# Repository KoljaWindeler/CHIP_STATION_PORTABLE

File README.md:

# CHIP_STATION_PORTABLE
This project is about a better and gaming compatible housing for C.H.I.P.

PocketChip is a great toy to play with, but the keys tend to be hard to push and make some hard click noises. 
The PSP seems like the perfect housing for a CHIP.

Just to mention some features:
 - it has a parallel display that was almost compatible with chip (only requires small amount of hardware)
 - many buttons (4 for the directions + 4 [x,y,a,b] + 2 shoulder buttons + menu buttons (vol+, vol-, ...) ..)
 - status LEDs for power / charging controllable on the LOW end (+5V is directly connected to the LED) 
 - 3.7V lipo battery which should work directly with chips battery circuit
 - 5V input for charging, perfect for chip
 
The purpose of this project is to create a mainboard that acts as an adapter between C.H.I.P. and the PSP.
It shall have the same form factor as the original PSP mainboard and connect easy to the existing flex connectors,
e.g. the buttons and the display. It shall also carry the DC/DC converter circuit to power the display backlight
and accomplish the conversion of the display signals. It shall also provide the required software and firmware files
for chip to use the PSP hardware.

All this will be documeted at https://bbs.nextthing.co/t/csp-chipstationportable/11171
JKW

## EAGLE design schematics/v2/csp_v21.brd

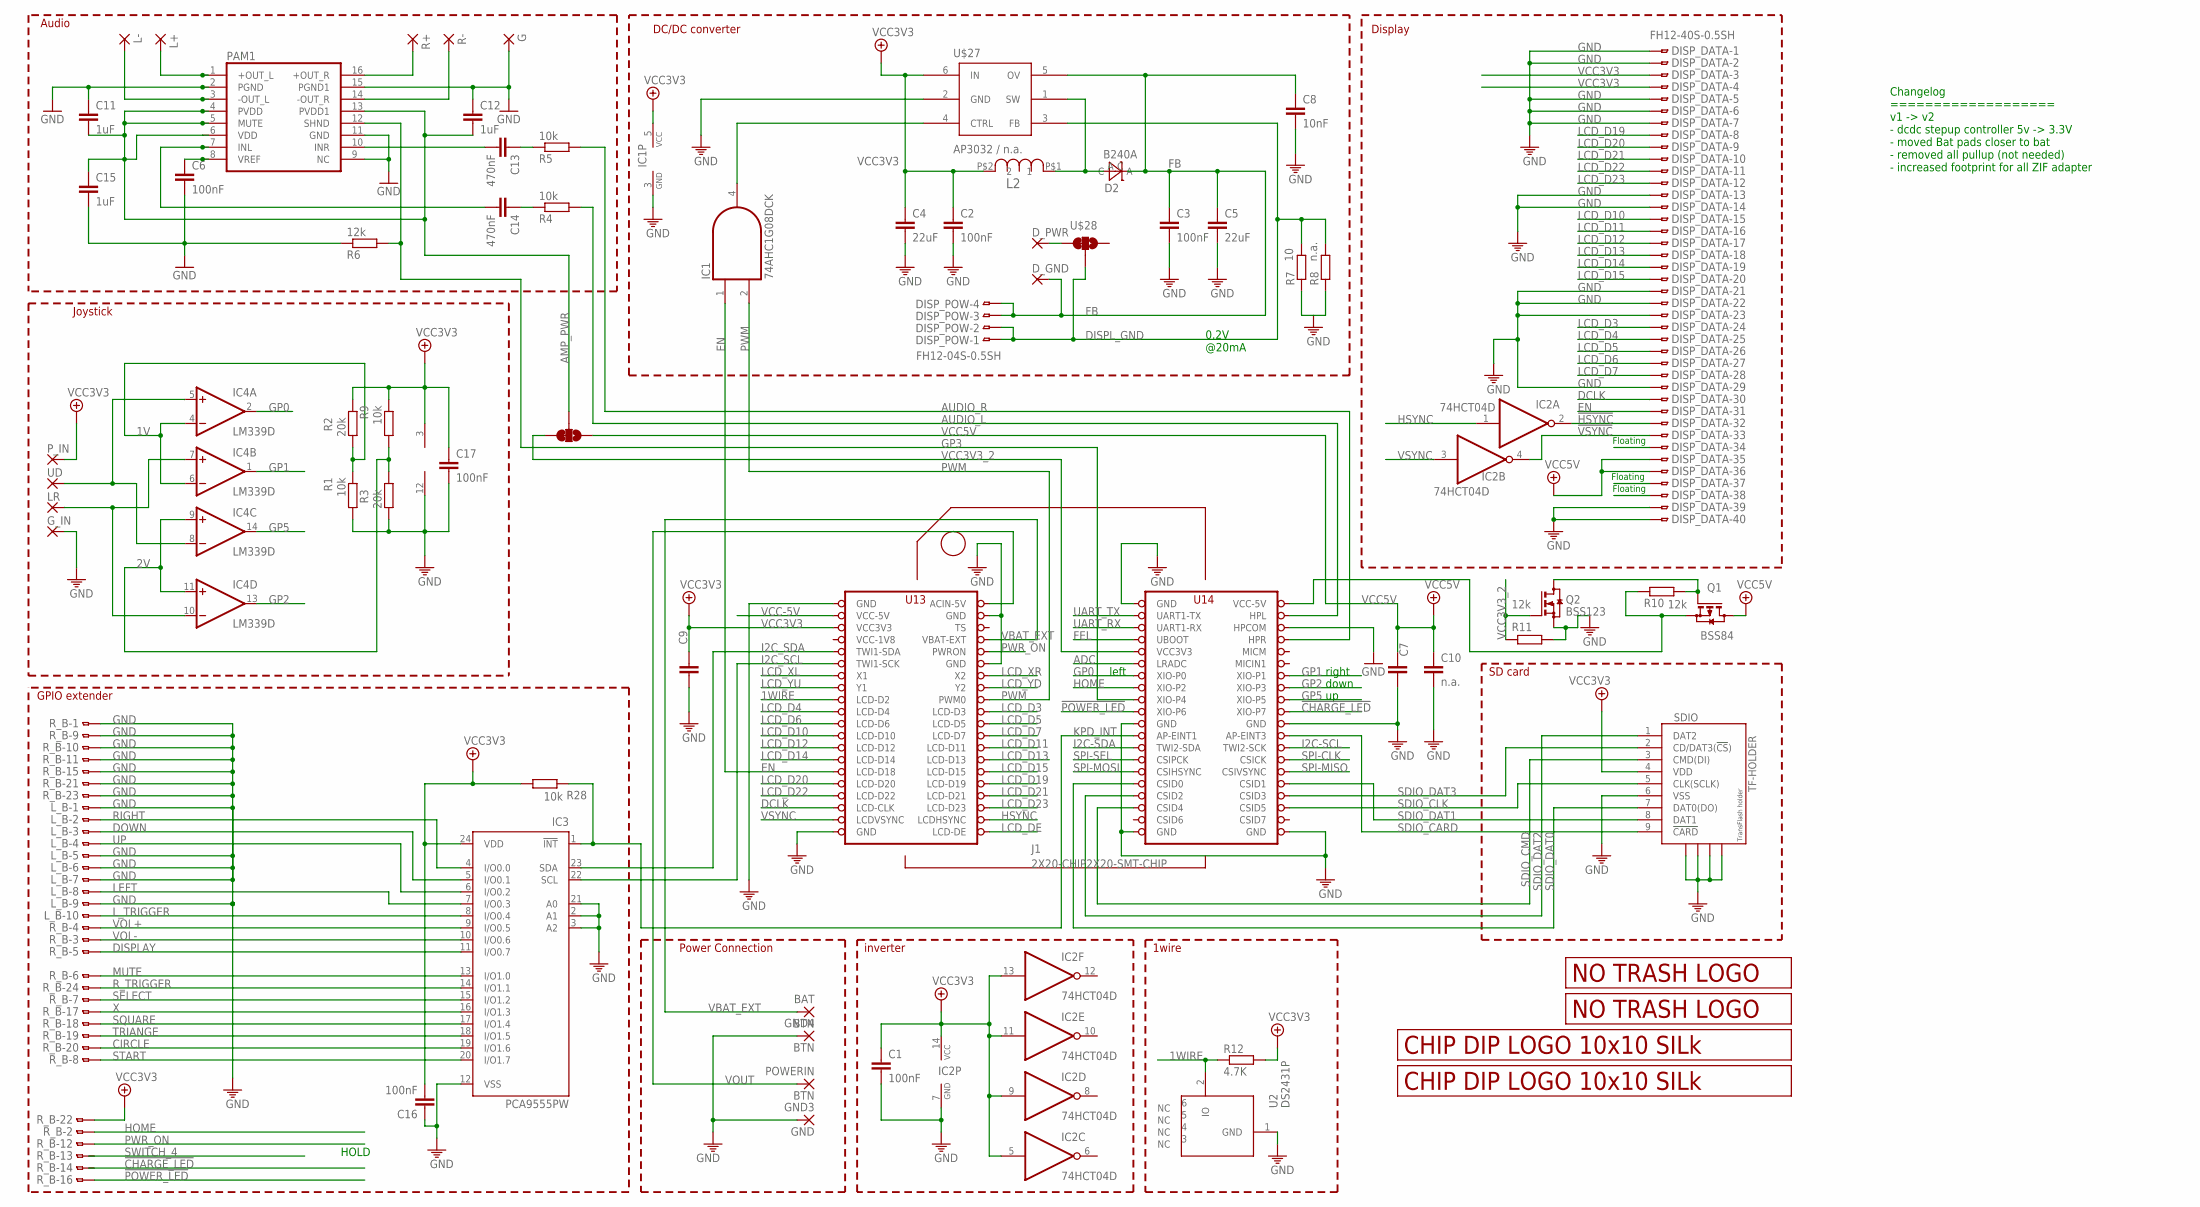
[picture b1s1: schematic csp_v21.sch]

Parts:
BAT: BTN; SMD1,27-2,54
C1, C2, C3, C6, C16, C17: 100nF; C0805
C4, C5: 22uF; C1206
C7, C9, C10: n.a.; C0805
C8: 10nF; C0805
C11, C12, C15: 1uF; C0805
C13, C14: 470nF; C0805
D2: B240A; DO-214AC
DISP_DATA: FH12-40S-0.5SH
DISP_POW: FH12-04S-0.5SH
D_GND: D_GND; SMD1,36-3
D_PWR: D_PWR; SMD1,36-3
G: 1,6/0,8
GND3: GND; SMD1,27-2,54
GND4: BTN; SMD1,27-2,54
G_IN: BTN; SMD1,36-3
IC1: 74AHC1G08DCK; SC70-5
IC2: 74HCT04D; SO14
IC3: PCA9555PW; TSSOP24
IC4: LM339D; SO14
J1: 2X20-CHIP2X20-SMT-CHIP; 2XAWHW40_G_SMD_R
L2: SRN6045-100M; SRN6045
L+: 1,6/0,8
L-: 1,6/0,8
LR: BTN; SMD1,36-3
L_B: FH12-10S-0.5SH
PAM1: PAM8403; SOP-16
POWERIN: BTN; SMD1,27-2,54
P_IN: BTN; SMD1,36-3
Q1: BSS84; SOT23
Q2: BSS123; SOT23
R1, R9, R28: 10k; M0805
R2, R3: 20k; M0805
R4, R5: 10k; R0805
R6, R10, R11: 12k; R0805
R7: 10; M0805
R8: n.a.; M0805
R12: 4.7K; M0805
R+: 1,6/0,8
R-: 1,6/0,8
R_B: FH12-24S-0.5SH
SDIO: TF-HOLDER; TF-PULL
SJ3: SMD_SJ_3WAY_CLOSED
U2: DS2431P; TSOC6
U$2, U$5: LOGO_10X10_SILK; LOGO2_10X10_SILK
U$3: LOGO_NO_TRASHROHS; LOGO_ROHS_SYM
U$4: LOGO_NO_TRASHNO_TRASH; LOGO_ROHS_NO_TRASH
U$27: AP3032 / n.a.; SOT23-6
U$28: SMD_SJ_3WAY_CLOSED
UD: BTN; SMD1,36-3

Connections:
1V: IC4.4 (-IN), IC4.6 (-IN), R1.1, R2.2
1WIRE: J1.LCD-D2, R12.1, U2.2 (IO)
2V: IC4.9 (+IN), IC4.11 (+IN), R3.1, R9.2
!CHARGE_LED: J1.XIO-P7, R_B.14
!HSYNC: DISP_DATA.32, IC2.2 (O)
!POWER_LED: J1.XIO-P6, R_B.16
!VSYNC: DISP_DATA.33, IC2.4 (O)
ADC: J1.LRADC
AMP_PWR: C11.2, C12.2, C15.1, PAM1.4 (PVDD), PAM1.5 (MUTE), PAM1.6 (VDD), PAM1.13 (PVDD1), SJ3.2
AUDIO_L: J1.HPL, R4.2
AUDIO_R: J1.HPR, R5.2
CIRCLE: IC3.19 (I/O1.6), R_B.20
DCLK: DISP_DATA.30, J1.LCD-CLK
DISPLAY: IC3.11 (I/O0.7), R_B.5
DISPL_GND: DISP_POW.1, DISP_POW.2, R7.2, R8.2, U$27.3 (FB), U$28.2
DOWN: IC3.5 (I/O0.1), L_B.3
EN: DISP_DATA.31, IC1.1 (I0), J1.LCD-D18
FB: C3.1, C5.1, C8.1, D2.C, DISP_POW.3, DISP_POW.4, D_GND.P$1, U$27.5 (OV)
FEL: J1.FEL (UBOOT)
GND: C1.2, C2.2, C3.2, C4.2, C5.2, C6.2, C7.2, C8.2, C9.2, C10.2, C11.1, C12.1, C15.2, C16.1, C17.2, DISP_DATA.1, DISP_DATA.2, DISP_DATA.5, DISP_DATA.6, DISP_DATA.7, DISP_DATA.13, DISP_DATA.14, DISP_DATA.21, DISP_DATA.22, DISP_DATA.23, DISP_DATA.29, DISP_DATA.39, DISP_DATA.40, G.1, GND3.1, GND4.1, G_IN.P$1, IC1.3 (GND), IC2.7 (GND), IC3.2 (A1), IC3.3 (A2), IC3.12 (VSS), IC3.21 (A0), IC4.12 (GND), J1.GND@1 (GND), J1.GND@2 (GND), J1.GND@3 (GND), J1.GND@4 (GND), J1.GND@5 (GND), J1.GND@6 (GND), J1.GND@7 (GND), J1.GND@8 (GND), J1.GND@10 (GND), J1.HPCOM, L_B.1, L_B.5, L_B.6, L_B.7, L_B.9, PAM1.2 (PGND), PAM1.9 (NC), PAM1.11 (GND), PAM1.15 (PGND1), Q2.2 (S), R1.2, R3.2, R6.1, R7.1, R8.1, R11.1, R_B.1, R_B.9, R_B.10, R_B.11, R_B.15, R_B.21, R_B.23, SDIO.6 (VSS), SDIO.S1, SDIO.S2, SDIO.S3, SDIO.S4, U2.1 (GND), U$27.2 (GND)
GP0: IC4.2 (OUT), J1.XIO-P0
GP1: IC4.1 (OUT), J1.XIO-P1
GP2: IC4.13 (OUT), J1.XIO-P3
GP3: J1.XIO-P4, PAM1.12 (SHND), R6.2
GP5: IC4.14 (OUT), J1.XIO-P5
HOME: J1.XIO-P2, R_B.2
HSYNC: IC2.1 (I), J1.LCD-HSYNC (LCDHSYNC)
I2C-SCL: J1.TWI2-SCK
I2C-SDA: J1.TWI2-SDA
I2C_SCL: IC3.22 (SCL), J1.TWI1-SCK
I2C_SDA: IC3.23 (SDA), J1.TWI1-SDA
INL: C14.2, PAM1.7 (INL)
INR: C13.2, PAM1.10 (INR)
KPD_INT: IC3.1 (!INT), J1.AP-EINT1, R28.1
L+OUT: L+.1, PAM1.1 (+OUT_L)
L-OUT: L-.1, PAM1.3 (-OUT_L)
LCD_D3: DISP_DATA.24, J1.LCD-D3
LCD_D4: DISP_DATA.25, J1.LCD-D4
LCD_D5: DISP_DATA.26, J1.LCD-D5
LCD_D6: DISP_DATA.27, J1.LCD-D6
LCD_D7: DISP_DATA.28, J1.LCD-D7
LCD_D10: DISP_DATA.15, J1.LCD-D10
LCD_D11: DISP_DATA.16, J1.LCD-D11
LCD_D12: DISP_DATA.17, J1.LCD-D12
LCD_D13: DISP_DATA.18, J1.LCD-D13
LCD_D14: DISP_DATA.19, J1.LCD-D14
LCD_D15: DISP_DATA.20, J1.LCD-D15
LCD_D19: DISP_DATA.8, J1.LCD-D19
LCD_D20: DISP_DATA.9, J1.LCD-D20
LCD_D21: DISP_DATA.10, J1.LCD-D21
LCD_D22: DISP_DATA.11, J1.LCD-D22
LCD_D23: DISP_DATA.12, J1.LCD-D23
LCD_DE: J1.LCD-DE
LCD_XL: J1.X1
LCD_XR: J1.X2
LCD_YD: J1.Y2
LCD_YU: J1.Y1
LEFT: IC3.7 (I/O0.3), L_B.8
L_TRIGGER: IC3.8 (I/O0.4), L_B.10
MUTE: IC3.13 (I/O1.0), R_B.6
unnamed: IC1.4 (O), U$27.4 (CTRL)
unnamed: J1.VCC-5V@2 (VCC-5V), Q1.2 (S), R10.2
unnamed: D_PWR.P$1, U$28.1
unnamed: IC4.5 (+IN), IC4.8 (-IN), UD.P$1
unnamed: IC4.7 (+IN), IC4.10 (-IN), LR.P$1
unnamed: Q1.1 (G), Q2.3 (D), R10.1
unnamed: C6.1, PAM1.8 (VREF)
unnamed: C14.1, R4.1
unnamed: C13.1, R5.1
PWM: IC1.2 (I1), J1.PWM0
PWR_ON: J1.PWRON, R_B.12
R+OUT: PAM1.16 (+OUT_R), R+.1
R-OUT: PAM1.14 (-OUT_R), R-.1
RIGHT: IC3.4 (I/O0.0), L_B.2
R_TRIGGER: IC3.14 (I/O1.1), R_B.24
SDIO_CARD: J1.AP-EINT3, SDIO.9 (!CARD)
SDIO_CLK: J1.CSID5, SDIO.5 (CLK(SCLK))
SDIO_CMD: J1.CISD4 (CSID4), SDIO.3 (CMD(DI))
SDIO_DAT0: J1.CSID0, SDIO.7 (DAT0(DO))
SDIO_DAT1: J1.CSID1, SDIO.8 (DAT1)
SDIO_DAT2: J1.CSID2, SDIO.1 (DAT2)
SDIO_DAT3: J1.CSID3, SDIO.2 (CD/DAT3(!CS!))
SELECT: IC3.15 (I/O1.2), R_B.7
SPI-CLK: J1.CSICK
SPI-MISO: J1.CSIVSYNC
SPI-MOSI: J1.CSIHYSYNC (CSIHSYNC)
SPI-SEL: J1.CSPICK (CSIPCK)
SQUARE: IC3.17 (I/O1.4), R_B.18
START: IC3.20 (I/O1.7), R_B.8
SWITCH_4: R_B.13
TRIANGE: IC3.18 (I/O1.5), R_B.19
UART_RX: J1.UART1-RX
UART_TX: J1.UART1-TX
UP: IC3.6 (I/O0.2), L_B.4
VBAT_EXT: BAT.1, J1.BAT (VBAT-EXT)
VCC3V3: C1.1, C2.1, C4.1, C9.1, C16.2, C17.1, DISP_DATA.3, DISP_DATA.4, IC1.5 (VCC), IC2.5 (I), IC2.9 (I), IC2.11 (I), IC2.13 (I), IC2.14 (VCC), IC3.24 (VDD), IC4.3 (V+), J1.VCC3V3@2 (VCC3V3), L2.P$2 (2), P_IN.P$1, R2.1, R9.1, R12.2, R28.2, R_B.22, SDIO.4 (VDD), U$27.6 (IN)
VCC3V3_2: J1.VCC3V3@1 (VCC3V3), Q2.1 (G), R11.2, SJ3.1
VCC5V: C7.1, C10.1, DISP_DATA.35, DISP_DATA.36, Q1.3 (D), SJ3.3
VCC-1V8: J1.VCC1V8 (VCC-1V8)
VCC-5V: J1.VCC-5V@1 (VCC-5V)
VOL+: IC3.9 (I/O0.5), R_B.4
VOL-: IC3.10 (I/O0.6), R_B.3
VOUT: J1.CHG-IN (ACIN-5V), POWERIN.1
VREG_OUTPUT: D2.A, L2.P$1 (1), U$27.1 (SW)
VSYNC: IC2.3 (I), J1.LCD-VSYNC (LCDVSYNC)
X: IC3.16 (I/O1.3), R_B.17

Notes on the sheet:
Power Connection
Audio
DC/DC converter
0.2V @20mA
Floating
HOLD
GPIO extender
SD card
Display
inverter
1wire
Changelog =================== v1 -> v2 - dcdc stepup controller 5v -> 3.3V - moved Bat pads closer to bat - removed all pullup (not needed) - increased footprint for all ZIF adapter
Joystick
left
right
down

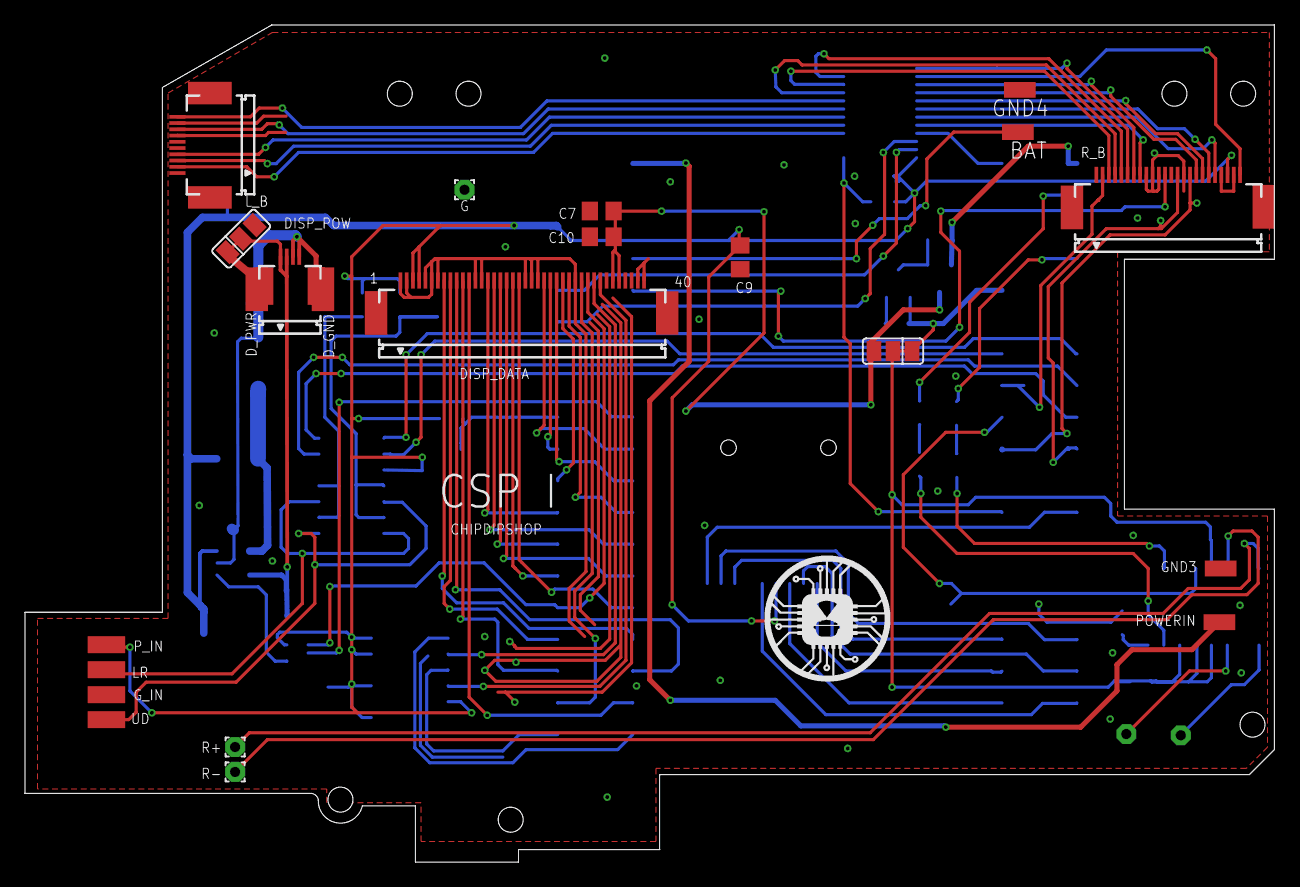
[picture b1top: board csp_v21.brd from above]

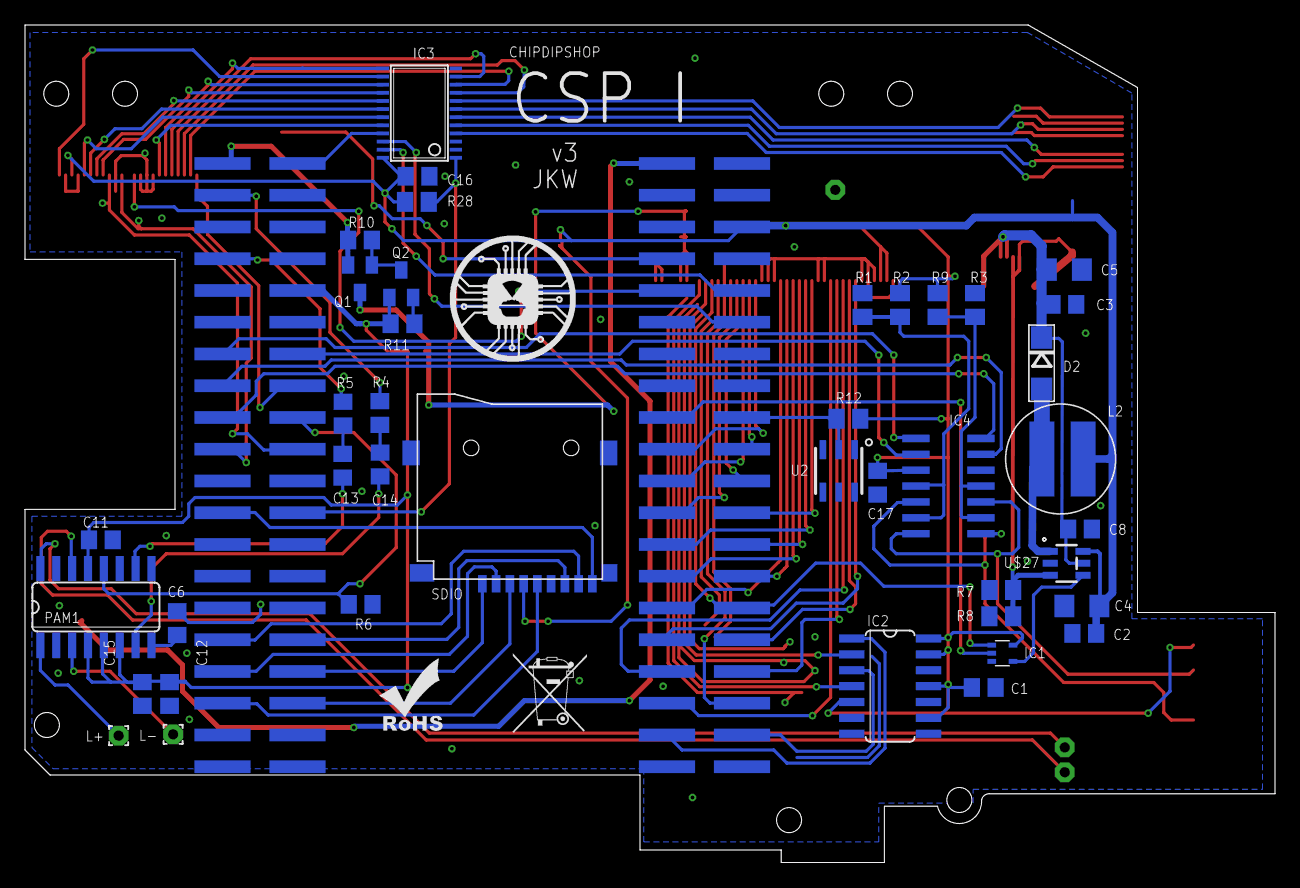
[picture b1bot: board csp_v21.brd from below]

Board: 2 copper layers, 100.0 x 67.0 mm, 68 parts (44 on the bottom side), 88 nets.

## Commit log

2016-11-06 init commit
2016-11-07 overlay added, untested
2016-11-07 added pre file and rearranged files for easy copy
2016-11-07 changed display driver to adopt to changes
2016-11-07 add eeprom image
2016-11-08 Create install.sh
    Added installation script
2016-11-08 added partly working dts
2016-11-08 removed override statement, extender working
2016-11-08 optimized schematic to one page
2016-11-15 added real keylayout
2016-11-16 flip p5 to p6 in schematic, to account for bug, no layout change
2016-11-17 init version of blink.sh
2016-11-17 added speaker scripts
2016-11-18 readded sd card
2016-11-18 fixed bugs
2016-11-18 added mmc
2016-11-18 added exec right
2016-11-23 added pdf
2016-11-24 changed to single page
2016-11-25 improved blink script
2016-11-27 changed from numblock to cursor
2016-11-27 moved left sholder to O 'Oh'
2016-11-28 moved overlay to central respo
2016-11-30 added v2 draft
2016-11-30 updated layout
2016-12-04 improved v2
2016-12-04 added gitignore
2016-12-08 replaced quote
2016-12-08 added v2.1, with 5V switchable to avoid discharge
2017-01-16 Fixed Op-amp, position of thumb still wrong
2017-02-12 moved pads for analog input
2017-04-08 added mouse scripts

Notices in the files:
parts and their libraries:
JKW_CHIP: License : http://creativecommons.org/licenses/by-sa/3.0
(Creative Commons 3.0)
